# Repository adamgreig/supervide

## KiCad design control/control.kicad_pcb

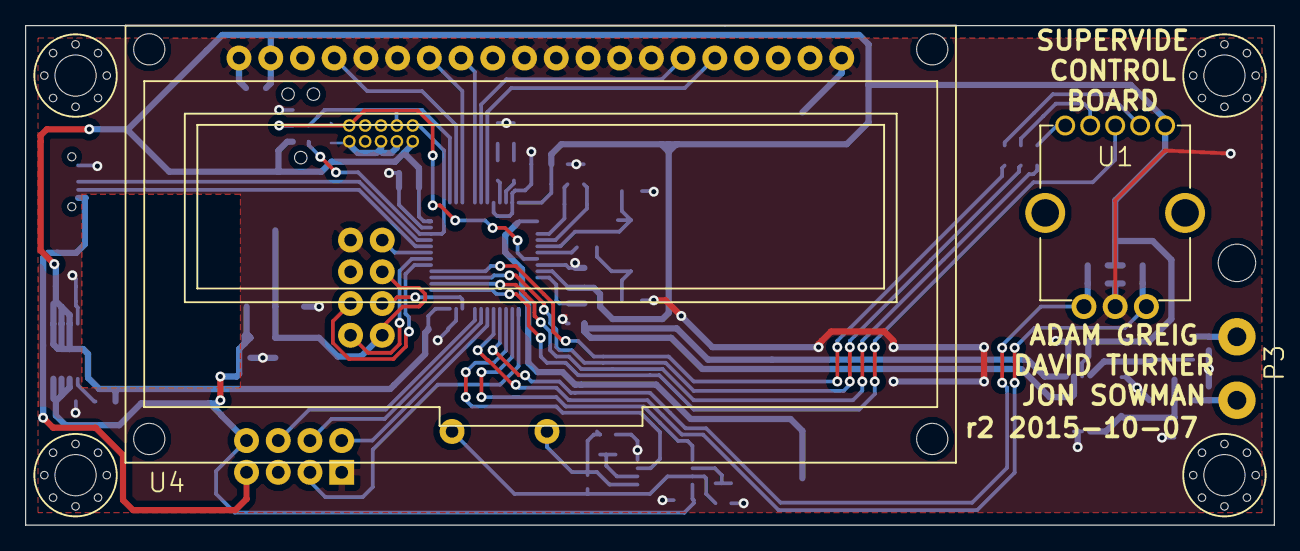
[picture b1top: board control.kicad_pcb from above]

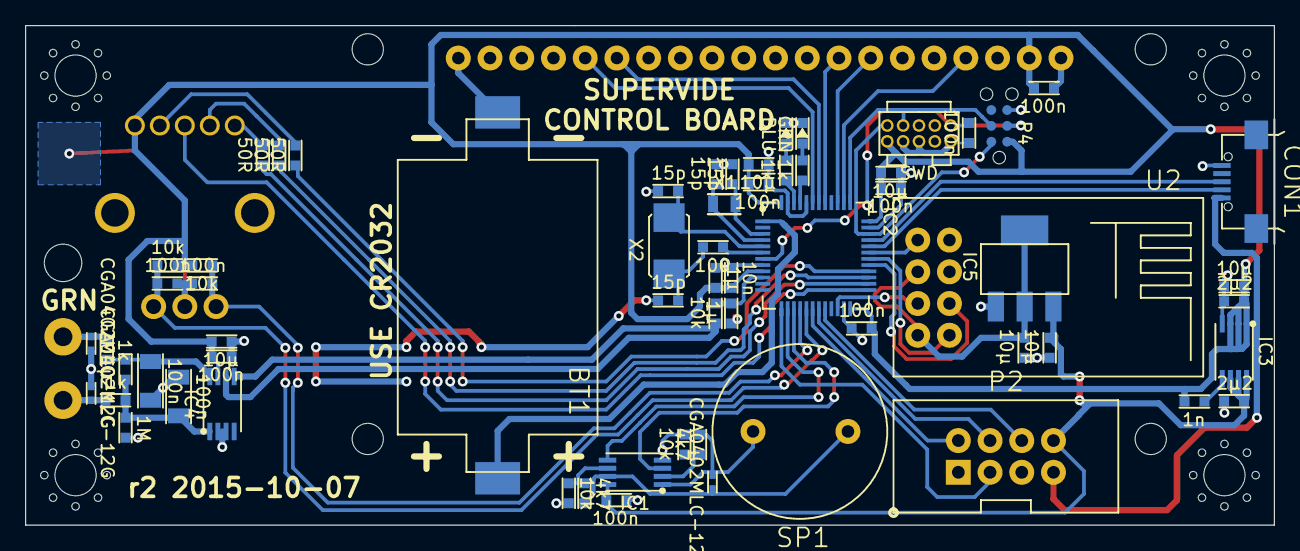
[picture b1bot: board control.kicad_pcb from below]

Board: 2 copper layers, 100.0 x 40.0 mm, 70 parts (63 on the bottom side), 55 nets.

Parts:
BT1: BATTERY; 2032HOLDER_KS1060
C1, C2, C6, C7, C8, C10, C13, C16, C26: 100n; C0603
C3, C4, C17, C21, C27, C28: 10µ; C0603
C5, C23, C24: 1µ; C0603
C9: 10n; C0603
C11, C12, C14, C15: 15p; C0603
C18, C20: 2µ2; C0603
C19: 1n; C0603
C22, C25: 100n; C1206
CON1: USB-MICRO-B; USB3065
D1, D2, D5: CGA0402MLC-12G; R0402
D3: GRN; LED0603
D4: BLU; LED0603
IC1: AD8542; MSOP8
IC2: STM32F072CBT6; LQFP48
IC3: ADP3335; MSOP8
IC4: AD8495; MSOP8
IC5: NCP1117; SOT223
P1: SWD; FTSH-105-01-F-D-K
P2: CONN_02X04; 2x4_100
P3: CONN_01X02; TC_K_PM
P4: CONN_02X03; TC2030-NL
R1, R5: 4k7; R0603
R2, R3, R4, R6, R9: 10k; R0603
R7: 100; R0603
R8, R10, R13, R14: 1k; R0603
R11: 1M; R0603
R12, R15, R16: 50R; R0603
SP1: SPEAKER; ABT-402-RC
U1: ROTENC; SF_ROTENC
U2: ESP8266-ESP01
U4: ER-OLEDM023-1
U5, U6, U7, U8: M3_HOLE; M3_MOUNT
X1: 32k768; R0805
X2: 8MHz; XTAL50x32

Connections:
+5V: CON1.1, P2.7
/CURRENT: IC2.13, P2.3
/ENC_A: C1.1, IC2.16, R2.2, U1.A
/ENC_B: C2.2, IC2.17, R4.2, U1.B
/ENC_BLU: IC2.28, R16.2
/ENC_GRN: IC2.27, R15.2
/ENC_RED: IC2.26, R12.2
/ENC_SW: IC2.25, U1.3
/M_RELAY: IC2.18, P2.2
/OLED_D/C: IC2.38, U4.4
/OLED_MOSI: IC2.41, U4.8
/OLED_SCLK: IC2.39, U4.7
/PH_RELAY: IC2.19, P2.4
/PIEZO_A: IC1.5, IC2.14
/PIEZO_B: IC1.3, IC2.15
/SWDCLK: IC2.37, P1.4, P4.4
/SWDIO: IC2.34, P1.2, P4.2
/THERMO: C24.1, IC2.10, R9.1
/TRIAC: IC2.20, P2.6
/USB_DM: CON1.2, IC2.32
/USB_DP: CON1.3, IC2.33
/WIFI_GP0: IC2.29, U2.2
/WIFI_RST: IC2.22, U2.7
/WIFI_RX: IC2.30, U2.1
/WIFI_TX: IC2.31, U2.5
/nRST: C10.1, IC2.7, P1.10, P4.3
/~OLED_CS: IC2.42, U4.15
/~OLED_RST: IC2.43, U4.16
GND: BT1.2, C1.2, C2.1, C3.2, C4.2, C5.2, C6.2, C7.2, C8.2, C9.2, C10.2, C11.1, C12.1, C13.2, C14.2, C15.2, C16.2, C17.2, C18.2, C20.2, C21.2, C22.1, C24.2, C25.2, C26.2, C27.2, C28.2, CON1.5, D1.1, D2.2, D3.1, D4.1, IC1.4, IC2.8, IC2.23, IC2.35, IC2.44, IC2.47, IC3.4, IC4.2, IC4.3, IC5.1, P1.3, P1.5, P1.9, P2.1, P4.5, R3.1, R6.1, R11.1, U1.C, U2.4, U4.1, U4.5, U4.6, U4.10, U4.11, U4.12, U4.13, U4.14, U4.20
unnamed: BT1.1, IC2.1
unnamed: C11.2, IC2.3, X1.1
unnamed: C12.2, IC2.4, X1.2
unnamed: C14.1, IC2.5, X2.2
unnamed: C15.1, R7.1, X2.1
unnamed: C19.2, IC3.5
unnamed: C22.2, C23.1, IC4.8, R8.1
unnamed: C23.2, C25.1, IC4.1, R10.1, R11.2
unnamed: C28.1, IC5.2, U2.6, U2.8
unnamed: D1.2, P3.2, R8.2
unnamed: D2.1, P3.1, R10.2
unnamed: D3.2, R13.1
unnamed: D4.2, R14.1
unnamed: D5.1, IC1.1, R1.1, SP1.1
unnamed: D5.2, IC1.7, R5.1, SP1.2
unnamed: IC1.2, R1.2, R3.2
unnamed: IC1.6, R5.2, R6.2
unnamed: IC2.6, R7.2
unnamed: IC2.45, R13.2
unnamed: IC2.46, R14.2
unnamed: IC4.5, IC4.6, R9.2
unnamed: R12.1, U1.1
unnamed: R15.1, U1.2
unnamed: R16.1, U1.4
VCC: C18.1, C26.1, C27.1, IC1.8, IC3.6, IC3.7, IC3.8, IC5.3, P2.8
VDD: C3.1, C4.1, C5.1, C6.1, C7.1, C8.1, C9.1, C13.1, C16.1, C17.1, C19.1, C20.1, C21.1, IC2.9, IC2.24, IC2.36, IC2.48, IC3.1, IC3.2, IC3.3, IC4.7, P1.1, P4.1, R2.1, R4.1, U1.5, U4.2

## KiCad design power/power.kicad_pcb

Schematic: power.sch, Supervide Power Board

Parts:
C1: 1nF; C_0805; Farnell 1759226
C2, C3: 100nF; C_0805; Farnell 1759166
C4: 22nF; C_1210; Farnell 2057310
D1: POWER; LED-0805; Farnell 2099239
D2: MASTER; LED-0805; Farnell 2099243
D3: PREHEAT; LED-0805; Farnell 2099236
D4: TRIAC; LED-0805; Farnell 1685055
D5, D6: MBR2H200SFT1G; SOD-123FL; Farnell 2452032
F1: 100mA; 5x20_clip; Farnell 1162740
F2: 13A; BS1362_clip; Farnell 1603990
K1: MASTER_LIVE; RZ03-1A4; Farnell 2325624
K2: PREHEAT; RZ03-1A4; Farnell 2325624
P1: CONTROL; 2x4_100; Farnell 2215303
P2: MAINS_INLET; GSP1_9103_no_protrude; Farnell 2080426
P3: LOAD_OUTLET; 5001_no_protrude; Farnell 2080465
P4: +5V; 1pin
P5: GND; 1pin
P6: I_SENSE; 1pin
Q1, Q2: BC817-40; SOT23; Farnell 1081223
R1, R4, R6: 390R; R_0805; Farnell 2331790
R2, R3, R5, R7: 300R; R_0805; Farnell 2138881
R8: 47R; C_1206; Farnell 1887414
R9: 300R; C_0805; Farnell 2331787
U1: VTX214; Farnell 2401030
U2: ACS710; SOIC16W-chunky; Farnell 1791411
U3: 70°C; WireConnection_1mmDrill; Farnell SN36219
U4: MOC3163-M; DIP-6__300_ELL; Farnell 1467853
U5: BTA16-800BRG; TO-220_Neutral123_Vertical_LargePads; Farnell 1057281

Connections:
+5V: C3.1, D1.1 (A), D2.1 (A), D3.1 (A), D5.1, D6.1, K1.2, K2.2, P1.8, P4.1, U1.3, U2.14; also elsewhere on the board
/EARTH: P2.1, P3.1
GND: C1.2, C2.2, C3.2, D4.2 (K), P1.1, P5.1, Q1.2, Q2.2, R3.2, R9.2, U1.4, U2.9, U2.16
I_SENSE: P1.3, P6.1, U2.12
LOAD_LIVE: K2.4, P3.3, R8.2, U5.1
LOAD_NEUTRAL: P3.2, U2.1, U2.2, U2.3, U2.4
MAINS_LIVE: F1.1, F2.2, K1.3
MAINS_NEUTRAL: P2.2, U1.2, U2.5, U2.6, U2.7, U2.8
MASTER_RELAY: P1.2, R1.2
unnamed: C1.1, U2.10
unnamed: C2.1, U2.11
unnamed: C4.2, R8.1
unnamed 12: D1.2 (K), R3.1; also elsewhere on the board
unnamed: D2.2 (K), R2.2
unnamed: D3.2 (K), R5.2
unnamed: D4.1 (A), R7.2
unnamed: D5.2, K1.1, Q1.3, R2.1
unnamed: D6.2, K2.1, Q2.3, R5.1
unnamed: F1.2, U1.1
unnamed: F2.1, P2.3
unnamed: Q1.1, R1.1
unnamed: Q2.1, R4.1
unnamed: R6.1, U3.1
unnamed: R6.2, U4.6 (S1)
unnamed: R9.1, U4.2 (K)
unnamed: U4.4 (S2), U5.3
PREHEAT_RELAY: P1.4, R4.2
TRIAC_MAINS: C4.1, K1.4, K2.3, U3.2, U5.2
TRIAC_TRIG: P1.6, R7.1, U4.1 (A)

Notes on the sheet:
LOAD CONTROL
POWER SUPPLY
CURRENT SENSE
CONNECTORS
56mV/A version: ACS710KLATR-12CB-T
Sets bandwidth with internal filter R
MAGIC BOX
5V 3W VTX-214-003-105
1000V/us min critical rise 5mA trigger current 12V typical inhibit voltage DIP-6
ORANGE
GREEN
RED
YELLOW
Heatsink: 1703170
ISOLATED TAB

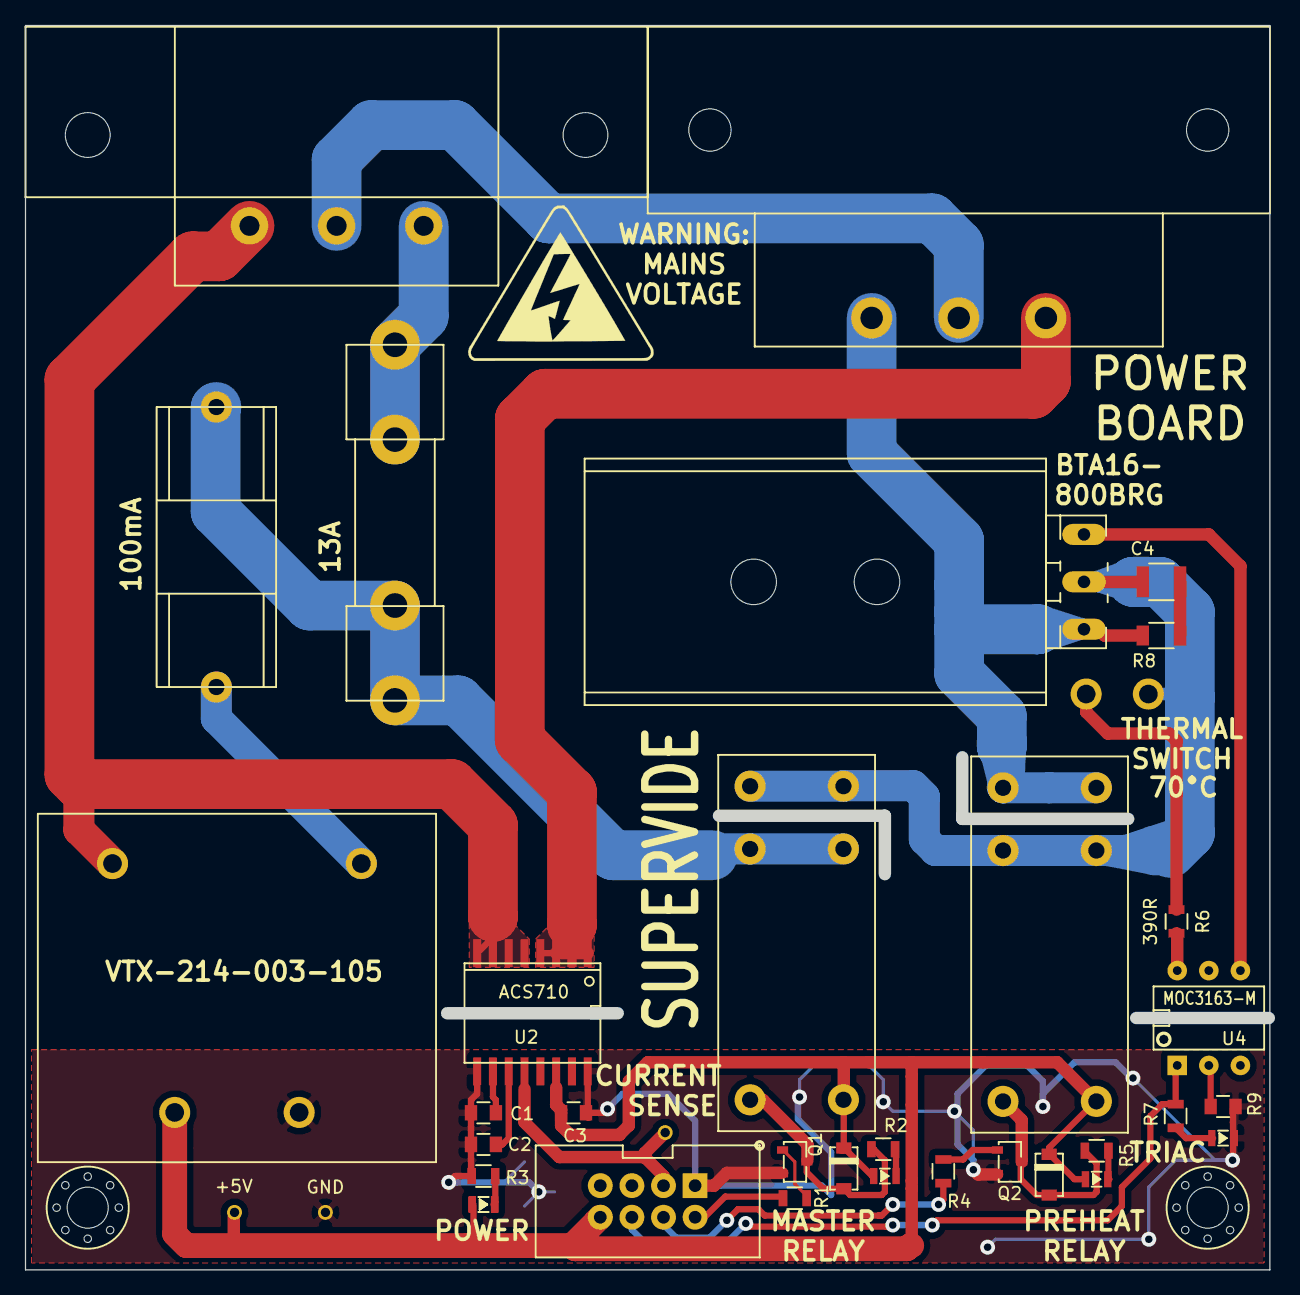
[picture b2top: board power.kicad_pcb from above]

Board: 2 copper layers, 99.5 x 99.1 mm, 39 parts (0 on the bottom side), 29 nets.

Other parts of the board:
D1#2: POWER; LED-0805
M3_MOUNT, M3_MOUNT#2: VAL**; M3_MOUNT

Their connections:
+5V: D1#2.1; also elsewhere on the board
unnamed 12: D1#2.2; also elsewhere on the board

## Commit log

2013-12-02 Rename project
2015-02-03 first go at control board schematic
2015-02-14 update sch: new oled, sync conditioning
2015-02-15 update sch: connection to power board
2015-02-18 Initial sketch of power schematic
2015-02-20 Removed PGA+RMS, added preheat relay
2015-02-21 SPST relays, filled in many values
2015-02-21 P sch: up2date connector, dbl winding xformer
2015-02-22 P sch: filled in most component part #s
2015-02-23 P sch: switcher PSU + tiny xover sense xformer
2015-02-24 Power: added TODO
2015-02-28 further work on control, start routing pcb
2015-02-28 Psch: crossover MOC, ds18b20, ERC
    * Changed MOC chip to one with builtin crossover, removed crossover sensing
    circuit.
    * Added DS18B20 temperature sensor (intended for mounting to the triac
    heatsink) on the pin previously used for crossover sense.
    * Minor changes around the PSU area to make ERC pass.
2015-03-01 Power footprints and associations
    Also first thoughts on PCB shape and connector placement
2015-03-02 Power: onboard fuses, better attempt at first pcb
2015-03-02 Removed neutral switching, more pcb mains rev
2015-03-03 Power: Thermal switch based cutoff
2015-03-04 first routing complete!
2015-03-04 some routing improvements
2015-03-04 Updated TRIAC part, added LEDs.
2015-03-04 P: Updated connector footprint and pinout
    Also decided to stick with ACS712 instead of cheaper/smaller ACS710 because the
    former is SOICW instead of SOIC so has a bit more isolation distance.
2015-03-05 Ppcb: first full route attempt
2015-03-06 update wifi, routing, gen gerbers, DONE r1
2015-03-06 fix a few derps, actually DONE r1
2015-03-06 Ppcb: triac heatsink and reroutes
2015-03-06 Ppcb: Gerbil export settings
2015-03-11 shift coin cell a little to make more space. still r1.
2015-03-28 Added *correct* heatsink to schematic.
2015-03-28 Stuff TODO/check
2015-03-29 Mostly LED value fixes, relay transistors
2015-03-29 Lots of footprint modifications
2015-03-30 Test points, rerouted relay drivers.
2015-03-30 regen gerbils w/ correct date on silk
2015-03-30 Silk, cleanup, masking, gerbils
2015-04-09 Power board BOM
2015-04-10 Added fuses to power BOM
2015-04-10 BOMs and gerbers
2015-04-19 add basic firmware layout
2015-04-20 mounting h/w for power board
2015-05-02 Add Rust support woo
2015-05-02 Firmware setup README and basic powerboard C drivers
2015-05-02 Starting attempt at control endplate SVG
2015-05-02 Architecture diagram and blurbs
2015-05-02 add autobuild of libcore.rlib
2015-05-02 have rust compilation depend on all rust files
2015-05-02 ChibiOS support lib, basic power driver
2015-05-02 put chibi/C code in subfolder
2015-07-06 More verbose/helpful README, file descriptions
2015-07-06 Added URLs to firmware readme
2015-07-06 Cleared up chibiOS default C main func
2015-07-06 PWM wrappers and TRIAC control driver
2015-07-06 Basic ADC driver and current conversion routine
2015-07-19 debug flash main.c
2015-07-28 Power: Added relay flyback diodes. Fixes #10
2015-09-07 Power: Triac pin spacing, removed extra relay pads
    Resolves #3
2015-10-04 Flipped SOT23 footprint. Fixes #1
2015-10-04 Bumped thermal switch drills. Fixes #2
2015-10-04 Added voltage warning, bumped rev+date
    Resolves #23 and resolves #6
2015-10-04 add -rescue lib of old symbolS
2015-10-04 add resistor to red LED, closes #4
2015-10-04 add strain relief for tc, closes #5
2015-10-04 add ldo for wifi, closes #7 probably
2015-10-04 update coin cell silk, closes #8
2015-10-04 Removed all traces of rust, untested C power driver
2015-10-04 smaller 32k xtal, closes #21
2015-10-04 add LEDs to control, closes #22
2015-10-04 add more resistors to rot end LEDs
2015-10-04 add tagconnect TC2030-CTX-NL footprint
2015-10-04 remove further rust related stuff
2015-10-04 shell over USB working, closes #19
2015-10-04 Update ChibiOS to latest
2015-10-04 DAC test. Ref #18
2015-10-07 rework buzzer driver to use non-inverting amplifiers
2015-10-07 move via slightly
2015-10-07 plot new gerbers
2015-10-07 swap to GPT2 for DAC timer
2015-10-07 Many minor fixes, resolves #25
2015-10-07 Updated gerber zip
2015-10-07 basic encoder stuff working
2015-10-07 add basic encoder switch support
2015-10-22 bom update
2015-10-23 Added power board BOM
2015-10-23 turn off lse for now
2015-10-23 screen test
2015-10-24 Added STM32F0-specific ADC conv grp settings
2015-10-24 Removed redundant chibisupport.c
2015-10-24 move main.c out of chibi folder
2015-10-24 update syntasic include list
2015-10-24 first go at oled driver
2015-10-24 longer wait for oled to reset
2015-10-24 Working TRIAC+relay driver and demo
2015-10-24 Used MS2ST for triac pwm timing.
    Resolves #27
2015-10-24 add cow icon
2015-10-24 add duck, fish, pig, sheep icons
2015-10-24 egg, thermometer icons
2015-10-24 Began new RMS current sensing thing
2015-10-24 Removed missing ADC config register
2015-10-24 small fix to oled driver to quash warning
2015-10-25 rotenc driver sort of thing
2015-10-25 RTC demo
2015-10-25 early work on beeper, not there yet
2015-10-25 better rot enc
2015-10-25 Added backup register demo
2015-10-25 oled icon draw now handles NULL icons
2015-10-25 disable LSE while one board still lacks it
2015-10-25 Moved clock/rtc stuff to clock.[c,h]
2015-10-25 Generalised menu structure
2015-10-25 somewhat better piezo...
2015-10-25 Cooking options and cook time
2015-10-25 Custom cook option
2015-10-25 Changed degrees to backtick in prep for custom char
2015-10-25 fix piezo dma business
2015-10-25 Config menu
2015-10-25 add variable beep lengths
2015-10-25 Wifi config skeletons
2015-10-25 basic thermocouple.
2015-10-29 cook ramblings
2015-11-01 Fixed R9 part number. Fixes #26
2015-11-09 Updated gitignore for vim backup/swap
2016-03-18 update thermo driver to convert to 0.1 C
2016-03-18 Added maketime/cooktime/countdown
2016-03-18 Ignore buildfiles
2016-03-18 Added cook labels
2016-03-18 Added gdb install to README
2016-03-18 Changed cook update timer to 200ms b/c aliasing
2016-03-18 Actually use maketime not mktime..........
2016-03-18 Rename display time/temp menu options
2016-03-18 fix returning from display thermo menu screen
2016-03-18 Remove power debug from main()
2016-03-18 First go at cook control
2016-03-18 ok basic cook control working
2016-03-18 fix temp display in custom input
2016-03-19 increase Kp
2016-03-19 tidy up main.c
2016-03-19 add live temperature plotting
2016-03-19 read and compensate for actual VREF voltage
2016-03-19 implement moving average filter and update liveplot to handle it
2016-03-30 start tasting notes
2016-03-30 further tasting
2016-04-05 First prototype of laser cuts
2016-04-06 Hardware shopping list
2016-04-06 Shortened end plates. FIxes #29
2016-04-06 Moved around IEC holes. Fixes #32, fixes #30
2016-04-06 Shortened power mounting plate. fixes #31
